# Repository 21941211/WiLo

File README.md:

# WiLo
Full documentation of the WiLo (Wireless Logger) LoRa enabled environmental monitoring logger.

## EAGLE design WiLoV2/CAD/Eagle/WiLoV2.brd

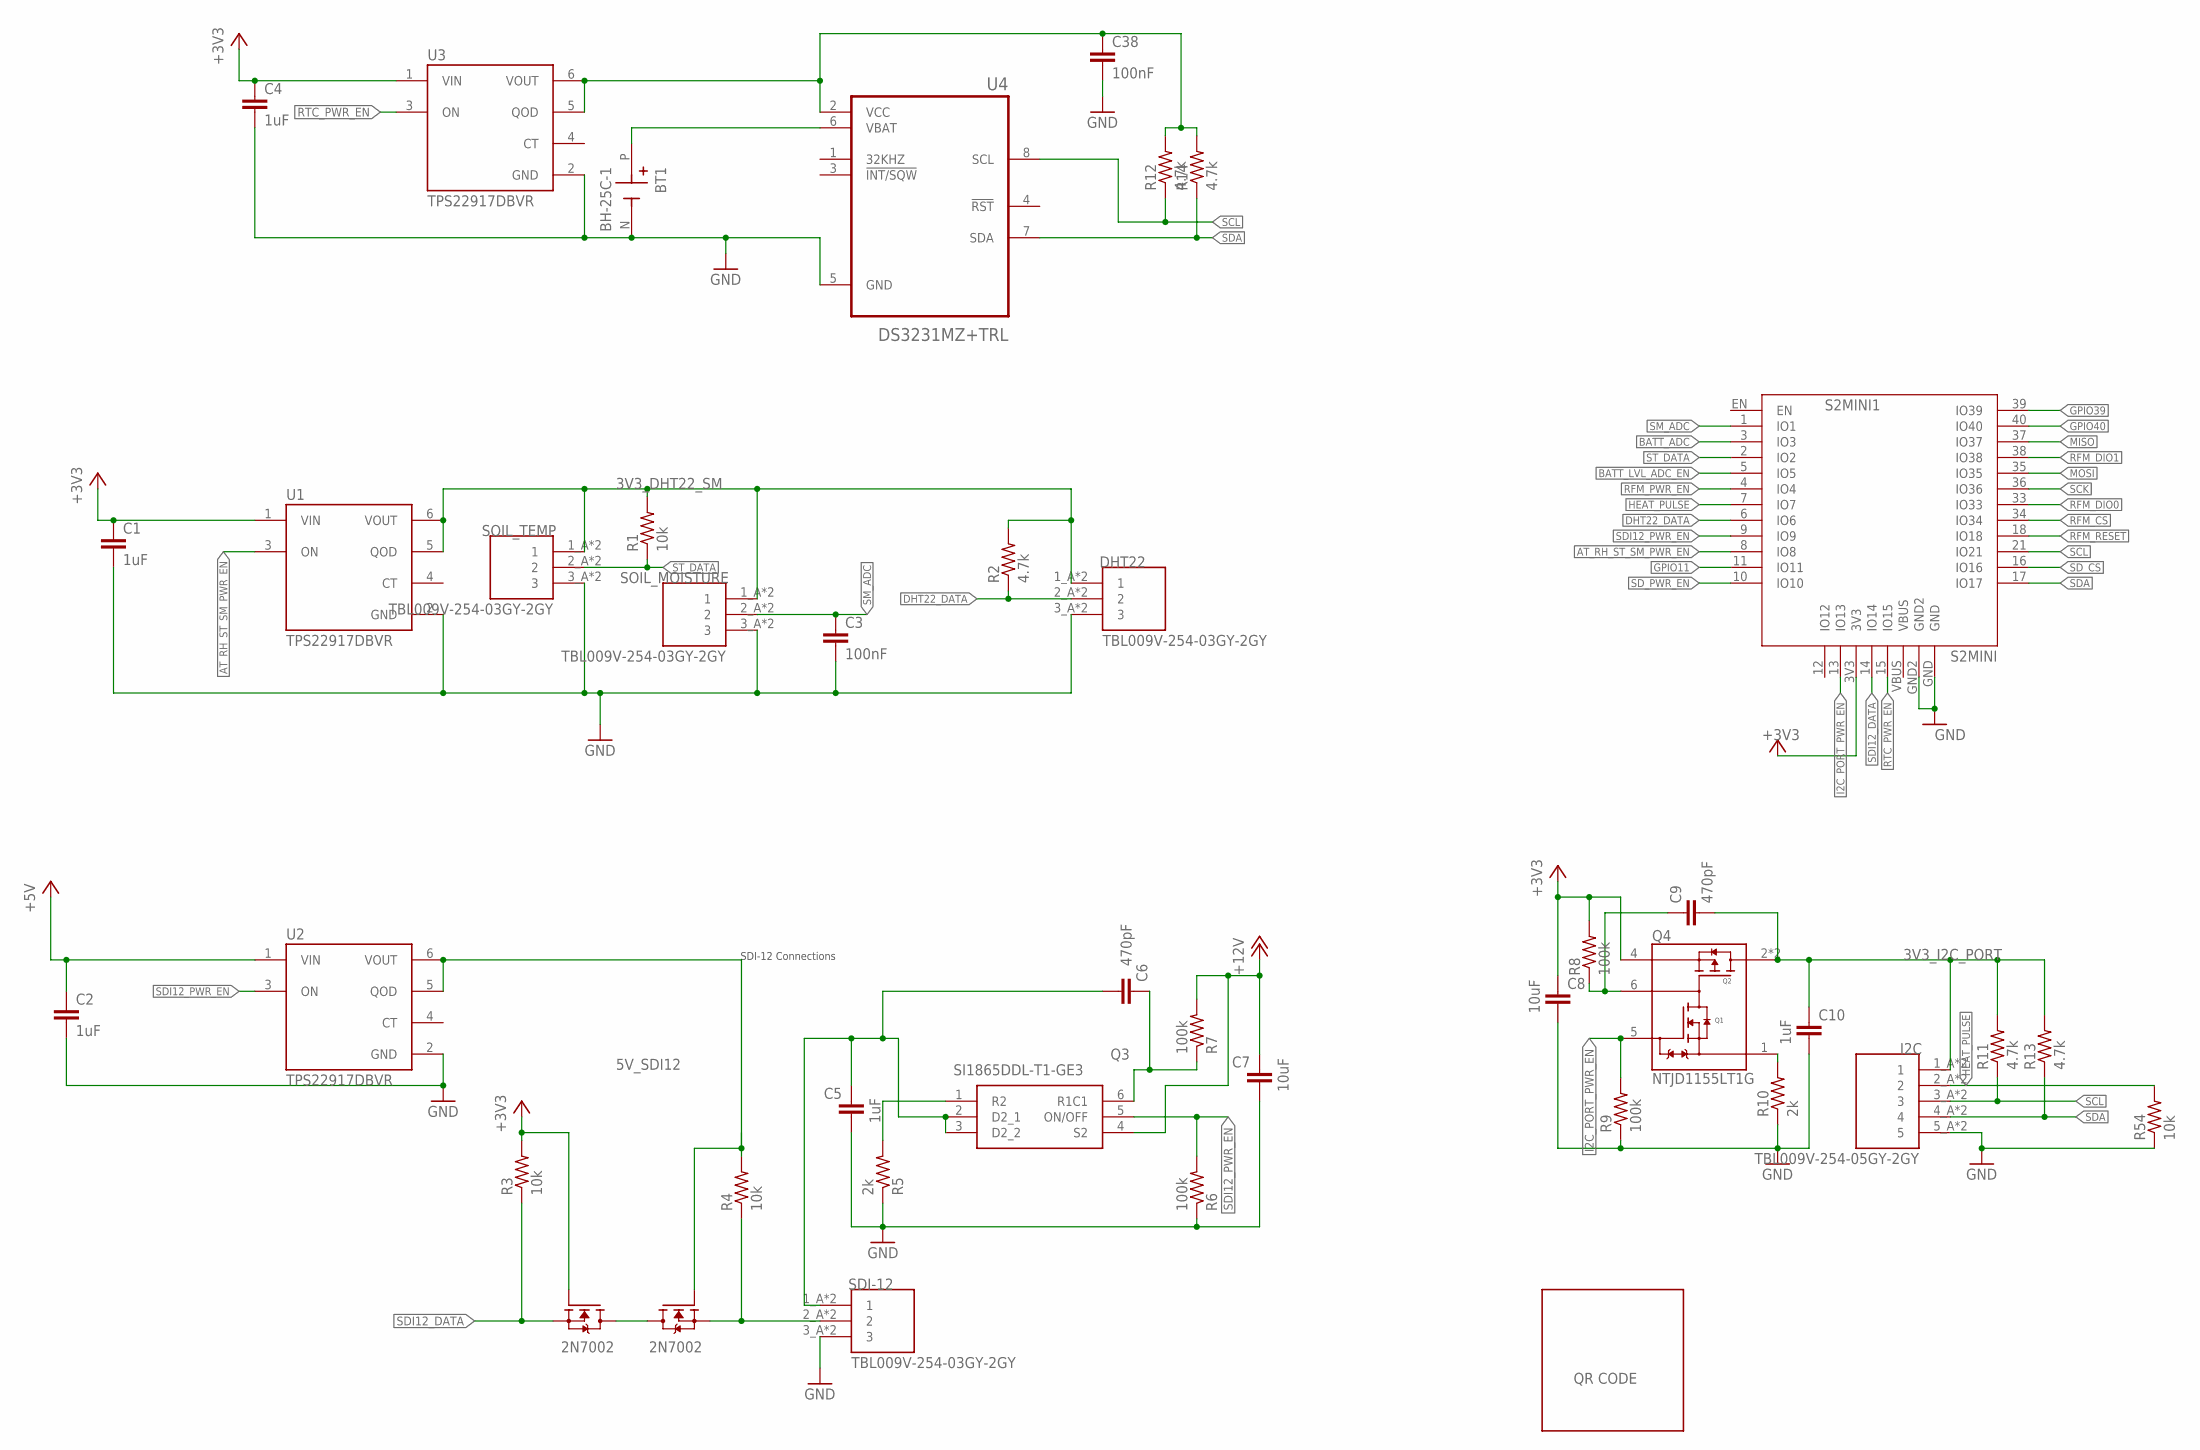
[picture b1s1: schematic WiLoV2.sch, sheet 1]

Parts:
BT1: BH-25C-1; BAT_BH-25C-1; MPN BH-25C-1
C1, C2, C4, C5, C10: 1uF; C0805; MPN CC0805KKX7R9BB105
C3, C38: 100nF; C0805; MPN KGM21NR71E104KT
C6, C9: 470pF; C0805; MPN CC0805JRNPOBBN471
C7, C8: 10uF; C0805; MPN GRM21BR61C106KE15K
DHT22: TBL009V-254-03GY-2GY; CUI_TBL009V-254-03GY-2GY; MPN TBL009V-254-03GY-2GY
I2C: TBL009V-254-05GY-2GY; CUI_TBL009V-254-05GY-2GY; MPN TBL009V-254-05GY-2GY
Q1, Q2: 2N7002; SOT95P240X111-3N; MPN 2N7002
Q3: SI1865DDL-T1-GE3; SOT65P210X110-6N; MPN SI1865DDL-T1-GE3
Q4: NTJD1155LT1G; TRANS_NTJD1155LT1G; MPN NTJD1155LT1G
QR_CODE: QR_CODE
R1, R3, R4, R54: 10k; R0603; MPN ERJ-U03F1002V
R2, R11, R12, R13, R14: 4.7k; R0603; MPN RK73G1JTTD4701C
R5, R10: 2k; R0603; MPN RC0603FR-072KL
R6, R7, R8, R9: 100k; R0603; MPN CRG0603F100K
S2MINI1: S2MINI
SDI-12: TBL009V-254-03GY-2GY; CUI_TBL009V-254-03GY-2GY; MPN TBL009V-254-03GY-2GY
SOIL_MOISTURE: TBL009V-254-03GY-2GY; CUI_TBL009V-254-03GY-2GY; MPN TBL009V-254-03GY-2GY
SOIL_TEMP: TBL009V-254-03GY-2GY; CUI_TBL009V-254-03GY-2GY; MPN TBL009V-254-03GY-2GY
U1, U2, U3: TPS22917DBVR; SOT95P280X145-6N; MPN TPS22917DBVT
U4: DS3231MZ+TRL; SOIC127P600X175-8N; MPN DS3231MZ+TRL

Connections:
3V3_DHT22_SM: DHT22.1_A (1), DHT22.1_B (1), R1.2, R2.2, SOIL_MOISTURE.1_A (1), SOIL_MOISTURE.1_B (1), SOIL_TEMP.1_A (1), SOIL_TEMP.1_B (1), U1.5 (QOD), U1.6 (VOUT)
3V3_I2C_PORT: C9.2, C10.1, I2C.1_A (1), I2C.1_B (1), Q4.2 (D2), Q4.3 (D2), R11.2, R13.2
5V_SDI12: Q2.1 (G), R4.2, U2.5 (QOD), U2.6 (VOUT)
+3V3: C1.1, C4.1, C8.1, Q1.1 (G), Q4.4 (S2), R3.2, R8.2, S2MINI1.3V3, U1.1 (VIN), U3.1 (VIN); also elsewhere on the board
+5V: C2.1, U2.1 (VIN); also elsewhere on the board
+12V: C7.1, Q3.4 (S2), R7.2; also elsewhere on the board
AT_RH_ST_SM_PWR_EN: S2MINI1.8 (IO8), U1.3 (ON)
BATT_ADC: S2MINI1.3 (IO3); also elsewhere on the board
BATT_LVL_ADC_EN: S2MINI1.5 (IO5); also elsewhere on the board
DHT22_DATA: DHT22.2_A (2), DHT22.2_B (2), R2.1, S2MINI1.6 (IO6)
GND: BT1.N, C1.2, C2.2, C3.2, C4.2, C5.2, C7.2, C8.2, C10.2, C38.2, DHT22.3_A (3), DHT22.3_B (3), I2C.5_A (5), I2C.5_B (5), R5.1, R6.1, R9.1, R10.1, R54.1, S2MINI1.GND, S2MINI1.GND2, SDI-12.3_A (3), SDI-12.3_B (3), SOIL_MOISTURE.3_A (3), SOIL_MOISTURE.3_B (3), SOIL_TEMP.3_A (3), SOIL_TEMP.3_B (3), U1.2 (GND), U2.2 (GND), U3.2 (GND), U4.5 (GND); also elsewhere on the board
GPIO11: S2MINI1.11 (IO11)
GPIO39: S2MINI1.39 (IO39)
GPIO40: S2MINI1.40 (IO40)
HEAT_PULSE: I2C.2_A (2), I2C.2_B (2), R54.2, S2MINI1.7 (IO7)
I2C_PORT_PWR_EN: Q4.5 (G1), R9.2, S2MINI1.13 (IO13)
MISO: S2MINI1.37 (IO37); also elsewhere on the board
MOSI: S2MINI1.35 (IO35); also elsewhere on the board
unnamed: Q1.3 (D), Q2.3 (D)
unnamed: C6.1, Q3.6 (R1C1), R7.1
unnamed: Q3.1 (R2), R5.2
unnamed: C9.1, Q4.6 (D1/G2), R8.1
unnamed: Q4.1 (S1), R10.2
unnamed: C5.1, C6.2, Q3.2 (D2_1), Q3.3 (D2_2), SDI-12.1_A (1), SDI-12.1_B (1)
unnamed: BT1.P, U4.6 (VBAT)
unnamed: C38.1, R12.2, R14.2, U3.5 (QOD), U3.6 (VOUT), U4.2 (VCC)
unnamed: Q2.2 (S), R4.1, SDI-12.2_A (2), SDI-12.2_B (2)
RFM_CS: S2MINI1.34 (IO34); also elsewhere on the board
RFM_DIO0: S2MINI1.33 (IO33); also elsewhere on the board
RFM_DIO1: S2MINI1.38 (IO38); also elsewhere on the board
RFM_PWR_EN: S2MINI1.4 (IO4); also elsewhere on the board
RFM_RESET: S2MINI1.18 (IO18); also elsewhere on the board
RTC_PWR_EN: S2MINI1.15 (IO15), U3.3 (ON)
SCK: S2MINI1.36 (IO36); also elsewhere on the board
SCL: I2C.3_A (3), I2C.3_B (3), R11.1, R12.1, S2MINI1.21 (IO21), U4.8 (SCL)
SDA: I2C.4_A (4), I2C.4_B (4), R13.1, R14.1, S2MINI1.17 (IO17), U4.7 (SDA)
SDI12_DATA: Q1.2 (S), R3.1, S2MINI1.14 (IO14)
SDI12_PWR_EN: Q3.5 (ON/OFF), R6.2, S2MINI1.9 (IO9), U2.3 (ON)
SD_CS: S2MINI1.16 (IO16); also elsewhere on the board
SD_PWR_EN: S2MINI1.10 (IO10); also elsewhere on the board
SM_ADC: C3.1, S2MINI1.1 (IO1), SOIL_MOISTURE.2_A (2), SOIL_MOISTURE.2_B (2)
ST_DATA: R1.1, S2MINI1.2 (IO2), SOIL_TEMP.2_A (2), SOIL_TEMP.2_B (2)

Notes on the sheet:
SDI-12 Connections

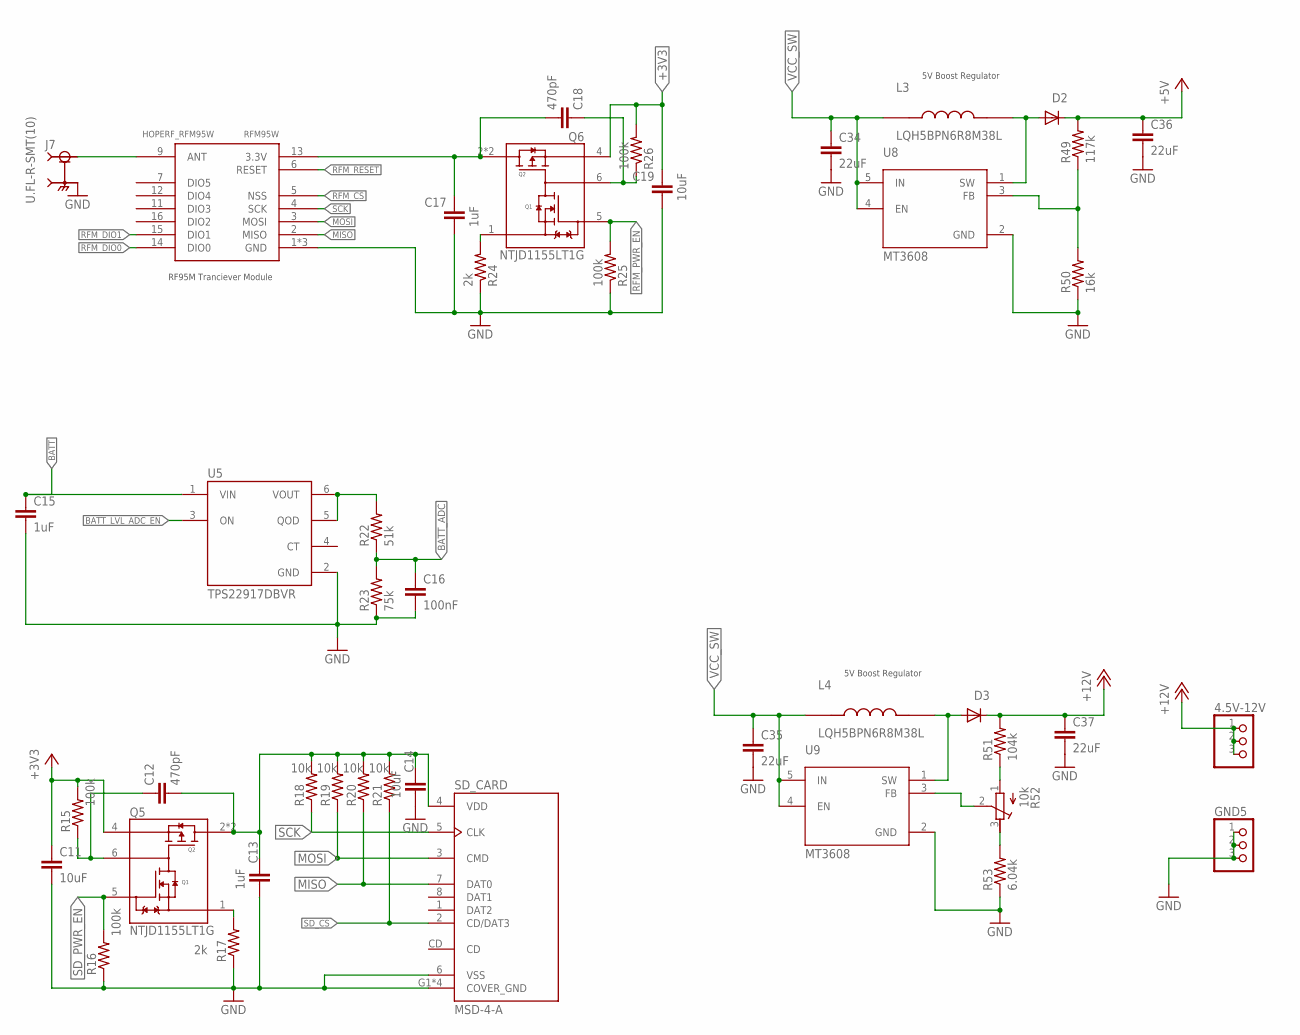
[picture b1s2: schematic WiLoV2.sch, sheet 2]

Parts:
4.5V-12V: PINHD-1X3; 1X03; MPN 61300311121
C11, C14, C19: 10uF; C0805; MPN GRM21BR61C106KE15K
C12, C18: 470pF; C0805; MPN CC0805JRNPOBBN471
C13, C15, C17: 1uF; C0805; MPN CC0805KKX7R9BB105
C16: 100nF; C0805; MPN KGM21NR71E104KT
C34, C35, C36, C37: 22uF; C0805; MPN CL21A226MOQNNNE
D2, D3: DIODE_SOD-123FL; SOD-123FL; MPN MBR120VLSFT1G
GND5: PINHD-1X3; 1X03; MPN 61300311121
J7: U.FL-R-SMT(10); HRS_U.FL-R-SMT(10); MPN U.FL-R-SMT-1(01)
L3, L4: LQH5BPN6R8M38L; IND_LQH5BPN6R8M38L; MPN LQH5BPN6R8M38L
Q5, Q6: NTJD1155LT1G; TRANS_NTJD1155LT1G; MPN NTJD1155LT1G
R15, R16, R25, R26: 100k; R0603; MPN CRG0603F100K
R17, R24: 2k; R0603; MPN RC0603FR-072KL
R18, R19, R20, R21: 10k; R0603; MPN ERJ-U03F1002V
R22: 51k; R0603; MPN RC0603FR-0751KL
R23: 75k; R0603; MPN AC0603FR-0775KL
R49: 117k; R0603; MPN RT0603DRE07117KL
R50: 16k; R0603; MPN RC0603FR-0716KL
R51: 104k; R0603; MPN RN73H1JTTD1043B50
R52: 10k; RTRIM3296W; MPN 3296W-1-103RLF
R53: 6.04k; R0603; MPN ERJ-3EKF6041V
RFM95W: HOPERF_RFM95W; MPN RFM95W-868S2
SD_CARD: MSD-4-A; CUI_MSD-4-A; MPN MSD-4-A
U5: TPS22917DBVR; SOT95P280X145-6N; MPN TPS22917DBVT
U8, U9: MT3608; SOT95P280X145-6N; MPN MT3608

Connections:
+3V3: C11.1, C19.1, Q5.4 (S2), Q6.4 (S2), R15.2, R26.2; also elsewhere on the board
+5V: C36.1, D2.C, R49.2; also elsewhere on the board
+12V: 4.5V-12V.1, 4.5V-12V.2, 4.5V-12V.3, C37.1, D3.C, R51.2; also elsewhere on the board
BATT: C15.1, U5.1 (VIN); also elsewhere on the board
BATT_ADC: C16.1, R22.1, R23.2; also elsewhere on the board
BATT_LVL_ADC_EN: U5.3 (ON); also elsewhere on the board
GND: C11.2, C13.2, C14.2, C15.2, C16.2, C17.2, C19.2, C34.2, C35.2, C36.2, C37.2, GND5.1, GND5.2, GND5.3, J7.2 (GND), J7.3 (GND), R16.1, R17.1, R23.1, R24.1, R25.1, R50.1, R53.1, RFM95W.1 (GND), RFM95W.8 (GND), RFM95W.10 (GND), SD_CARD.6 (VSS), SD_CARD.G1 (COVER_GND), SD_CARD.G2 (COVER_GND), SD_CARD.G3 (COVER_GND), SD_CARD.G4 (COVER_GND), U5.2 (GND), U8.2 (GND), U9.2 (GND); also elsewhere on the board
MISO: R20.1, RFM95W.2 (MISO), SD_CARD.7 (DAT0); also elsewhere on the board
MOSI: R19.1, RFM95W.3 (MOSI), SD_CARD.3 (CMD); also elsewhere on the board
unnamed: R22.2, U5.5 (QOD), U5.6 (VOUT)
unnamed: R51.1, R52.1 (A)
unnamed: D3.A, L4.2, U9.1 (SW)
unnamed: R52.2 (S), U9.3 (FB)
unnamed: R52.3 (E), R53.2
unnamed: C12.1, Q5.6 (D1/G2), R15.1
unnamed: Q5.1 (S1), R17.2
unnamed: D2.A, L3.2, U8.1 (SW)
unnamed: J7.1 (SIG), RFM95W.9 (ANT)
unnamed: R49.1, R50.2, U8.3 (FB)
unnamed: C12.2, C13.1, C14.1, Q5.2 (D2), Q5.3 (D2), R18.2, R19.2, R20.2, R21.2, SD_CARD.4 (VDD)
unnamed: C18.1, Q6.6 (D1/G2), R26.1
unnamed: Q6.1 (S1), R24.2
unnamed: C17.1, C18.2, Q6.2 (D2), Q6.3 (D2), RFM95W.13 (3.3V)
RFM_CS: RFM95W.5 (NSS); also elsewhere on the board
RFM_DIO0: RFM95W.14 (DIO0); also elsewhere on the board
RFM_DIO1: RFM95W.15 (DIO1); also elsewhere on the board
RFM_PWR_EN: Q6.5 (G1), R25.2; also elsewhere on the board
RFM_RESET: RFM95W.6 (RESET); also elsewhere on the board
SCK: R18.1, RFM95W.4 (SCK), SD_CARD.5 (CLK); also elsewhere on the board
SD_CS: R21.1, SD_CARD.2 (CD/DAT3); also elsewhere on the board
SD_PWR_EN: Q5.5 (G1), R16.2; also elsewhere on the board
VCC_SW: C34.1, C35.1, L3.1, L4.1, U8.4 (EN), U8.5 (IN), U9.4 (EN), U9.5 (IN); also elsewhere on the board

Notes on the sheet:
RF95M Tranciever Module
5V Boost Regulator

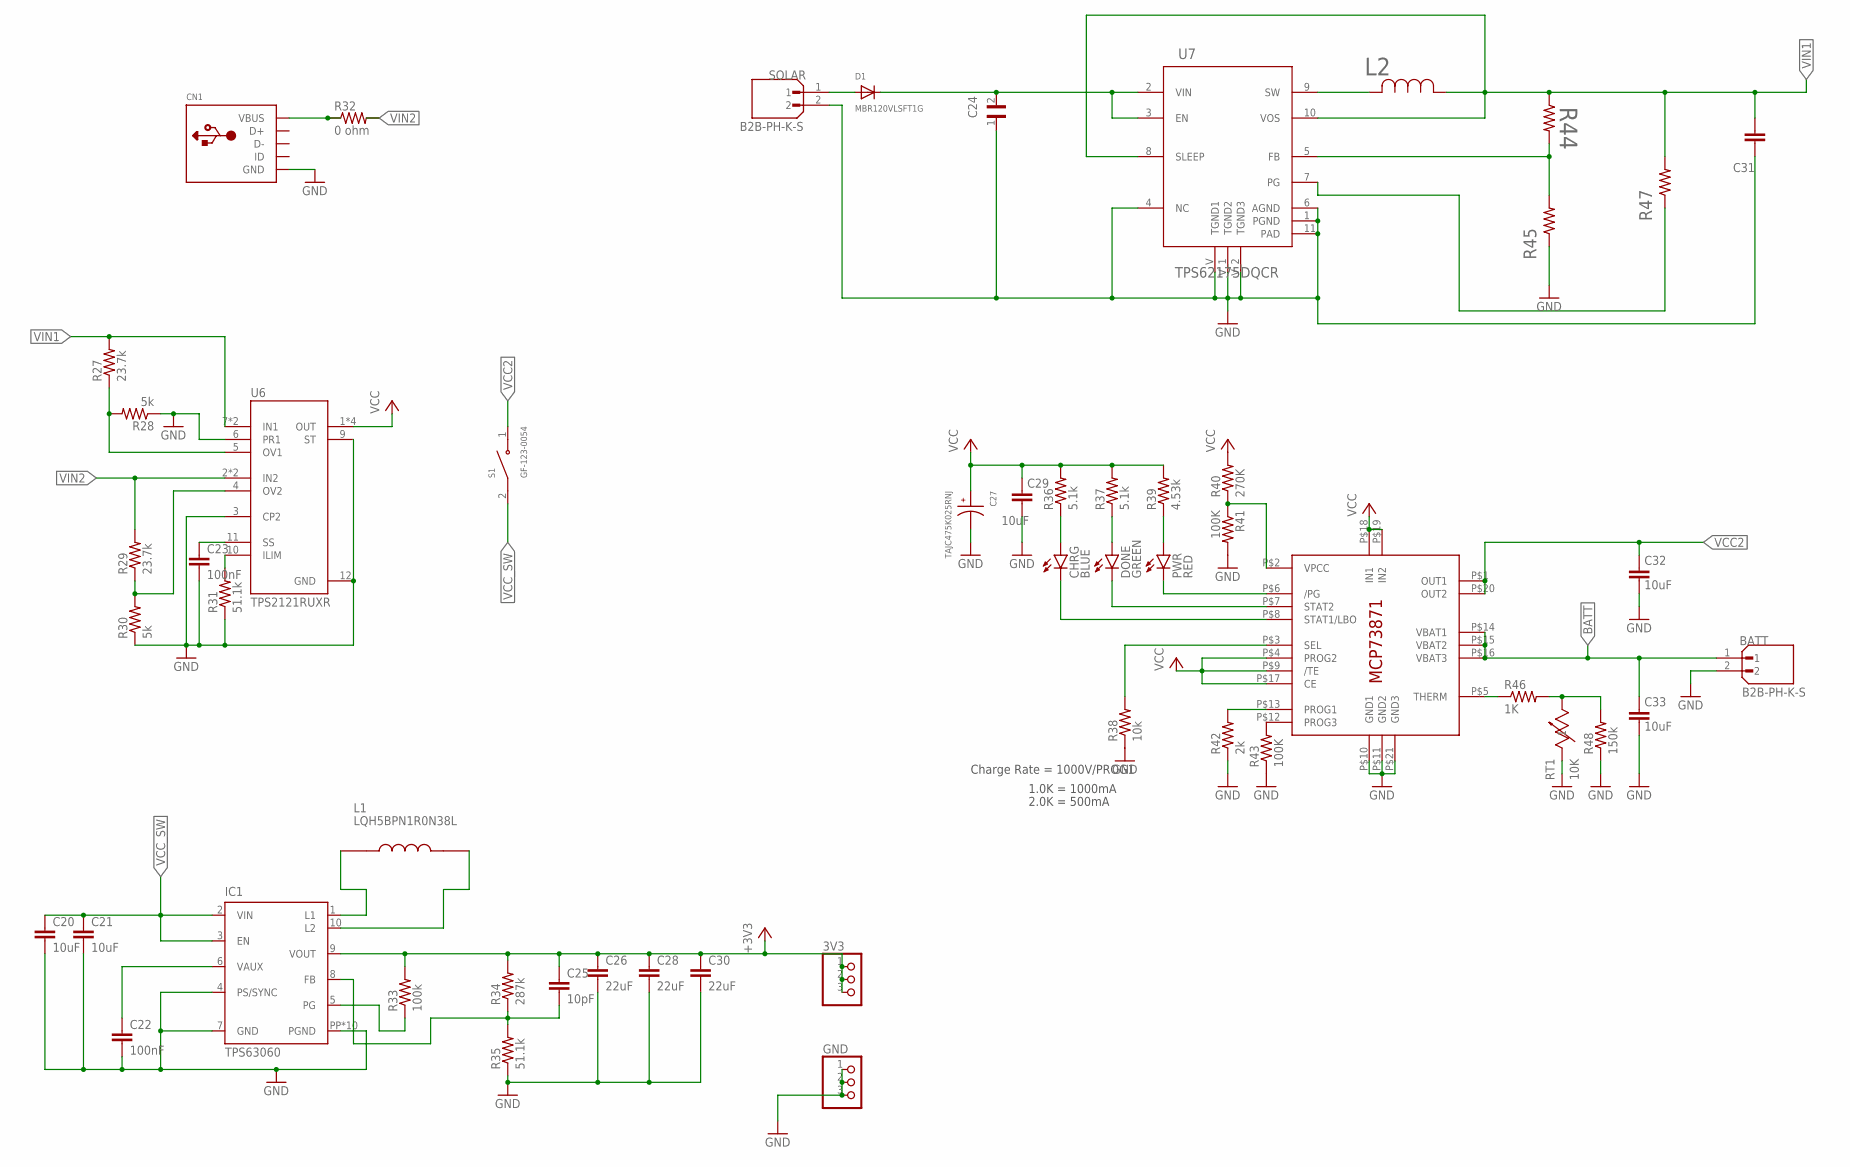
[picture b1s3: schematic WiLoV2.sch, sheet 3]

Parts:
3V3: PINHD-1X3; 1X03; MPN 61300311121
BATT: B2B-PH-K-S; JST_B2B-PH-K-S; MPN B2B-PH-K-S
C20, C21, C29, C32, C33: 10uF; C0805; MPN GRM21BR61C106KE15K
C22, C23: 100nF; C0805; MPN KGM21NR71E104KT
C24: 2.2uF; CAPC2012X145N; MPN CGA4J3X7R1H225K125AB
C25: 10pF; C0805; MPN C0805C100JDGACTU
C26, C28, C30, C31: 22uF; C0805; MPN CL21A226MOQNNNE
C27: TAJC475K025RNJ; CAPPM6032X280N; MPN TAJC475K025RNJ
CHRG: BLUE; SML0603; MPN XZCFBB53W-8VF
CN1: USBMINIB; USB-MINIB; MPN 690-005-299-043
D1: MBR120VLSFT1G; SOD-123FL; MPN MBR120VLSFT1G
DONE: GREEN; SML0603; MPN XZCDGK53W-8VF
GND: PINHD-1X3; 1X03; MPN 61300311121
IC1: TPS63060; DSC-S-PWSON-N10; MPN TPS63060DSCR
IC2: MCP73871; QFN20_4MM; MPN MCP73871T-2CCI/ML
L1: LQH5BPN1R0N38L; IND_LQH5BPN1R0N38L; MPN LQH5BPN1R0N38L
L2: 10uH; IND_IFSC_1515AH_VIS-M; MPN IFSC1515AHER100M01
PWR: RED; SML0603; MPN XZCM2CRK53WA-8VF
R27, R29: 23.7k; R0603; MPN ERJ-3EKF2372V
R28, R30: 5k; R0603; MPN RN73A1J5K0FTD
R31, R35: 51.1k; R0603; MPN RC0603FR-0751K1L
R32: 0 ohm; R0805; MPN ERJ-6GEY0R00V
R33, R47: 100k; R0603; MPN CRG0603F100K
R34: 287k; R0603; MPN ERJ-3EKF2873V
R36, R37: 5.1k; R0603; MPN ERA-3ARW512V
R38: 10k; R0603; MPN ERJ-U03F1002V
R39: 4.53k; R0603; MPN ERJ-3EKF4531V
R40: 270K; R0603; MPN ERJ-3EKF2703V
R41, R43: 100K; R0805; MPN RC0805FR-07100KL
R42: 2k; R0603; MPN RC0603FR-072KL
R44: 105k; R0603; MPN AC0603FR-07105KL
R45: 20k; R0603; MPN RC0603FR-0720KL
R46: 1K; R0603; MPN RMCF0603FT1K00
R48: 150k; R0603; MPN ERJ-3EKF1503V
RT1: 10K; G1_USS; MPN 103JG1F
S1: GF-123-0054; SW_GF-123-0054; MPN GF-123-0054
SOLAR: B2B-PH-K-S; JST_B2B-PH-K-S; MPN B2B-PH-K-S
U6: TPS2121RUXR; IC_TPS2121RUXR; MPN TPS2121RUXR
U7: TPS62175DQCR; DQC0010A; MPN TPS62175DQCR

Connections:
+3V3: 3V3.1, 3V3.2, 3V3.3, C25.1, C26.1, C28.1, C30.1, IC1.9 (VOUT), R33.2, R34.2; also elsewhere on the board
BATT: BATT.1, C33.1, IC2.P$14 (VBAT1), IC2.P$15 (VBAT2), IC2.P$16 (VBAT3); also elsewhere on the board
GND: BATT.2, C20.2, C21.2, C22.2, C23.2, C24.1, C26.2, C27.2, C28.2, C29.2, C30.2, C31.1, C32.2, C33.2, CN1.GND, GND.1, GND.2, GND.3, IC1.4 (PS/SYNC), IC1.7 (GND), IC1.PP (PGND), IC1.PP@1 (PGND), IC1.PP@2 (PGND), IC1.PP@3 (PGND), IC1.PP@4 (PGND), IC1.PP@5 (PGND), IC1.PP@7 (PGND), IC1.PP@8 (PGND), IC1.PP@9 (PGND), IC1.PP@10 (PGND), IC2.P$10 (GND1), IC2.P$11 (GND2), IC2.P$21 (GND3), R28.1, R30.1, R31.1, R35.1, R38.1, R41.2, R42.1, R43.1, R45.1, R48.1, RT1.1, SOLAR.2, U6.3 (CP2), U6.6 (PR1), U6.9 (ST), U6.12 (GND), U7.1 (PGND), U7.4 (NC), U7.6 (AGND), U7.11 (PAD), U7.V (TGND1), U7.V_1 (TGND2), U7.V_2 (TGND3); also elsewhere on the board
unnamed: IC1.1 (L1), L1.1
unnamed: IC1.10 (L2), L1.2
unnamed: C22.1, IC1.6 (VAUX)
unnamed: IC1.5 (PG), R33.1
unnamed: IC2.P$6 (/PG), PWR.C
unnamed: DONE.C, IC2.P$7 (STAT2)
unnamed: CHRG.C, IC2.P$8 (STAT1/LBO)
unnamed: CHRG.A, R36.1
unnamed: DONE.A, R37.1
unnamed: PWR.A, R39.1
unnamed: IC2.P$12 (PROG3), R43.2
unnamed: IC2.P$13 (PROG1), R42.2
unnamed: C24.2, D1.C, U7.2 (VIN), U7.3 (EN)
unnamed: IC2.P$5 (THERM), R46.1
unnamed: R46.2, R48.2, RT1.2
unnamed: CN1.VBUS, R32.1
unnamed: C25.2, IC1.8 (FB), R34.1, R35.2
unnamed: L2.2, U7.9 (SW)
unnamed: R44.2, R45.2, U7.5 (FB)
unnamed: R47.1, U7.7 (PG)
unnamed: R27.1, R28.2, U6.5 (OV1)
unnamed: R29.1, R30.2, U6.4 (OV2)
unnamed: R31.2, U6.10 (ILIM)
unnamed: C23.1, U6.11 (SS)
unnamed: IC2.P$3 (SEL), R38.2
unnamed: D1.A, SOLAR.1
VCC: C27.1, C29.1, IC2.P$4 (PROG2), IC2.P$9 (/TE), IC2.P$17 (CE), IC2.P$18 (IN1), IC2.P$19 (IN2), R36.2, R37.2, R39.2, R40.2, U6.1 (OUT), U6.1_1 (OUT), U6.8 (OUT), U6.8_1 (OUT)
VCC2: C32.1, IC2.P$1 (OUT1), IC2.P$20 (OUT2), S1.1
VCC_SW: C20.1, C21.1, IC1.2 (VIN), IC1.3 (EN), S1.2; also elsewhere on the board
VIN1: C31.2, L2.1, R27.2, R44.1, R47.2, U6.7 (IN1), U6.7_1 (IN1), U7.8 (SLEEP), U7.10 (VOS)
VIN2: R29.2, R32.2, U6.2 (IN2), U6.2_1 (IN2)
VPCC: IC2.P$2 (VPCC), R40.1, R41.1

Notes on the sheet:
Charge Rate = 1000V/PROG1
1.0K = 1000mA
2.0K = 500mA

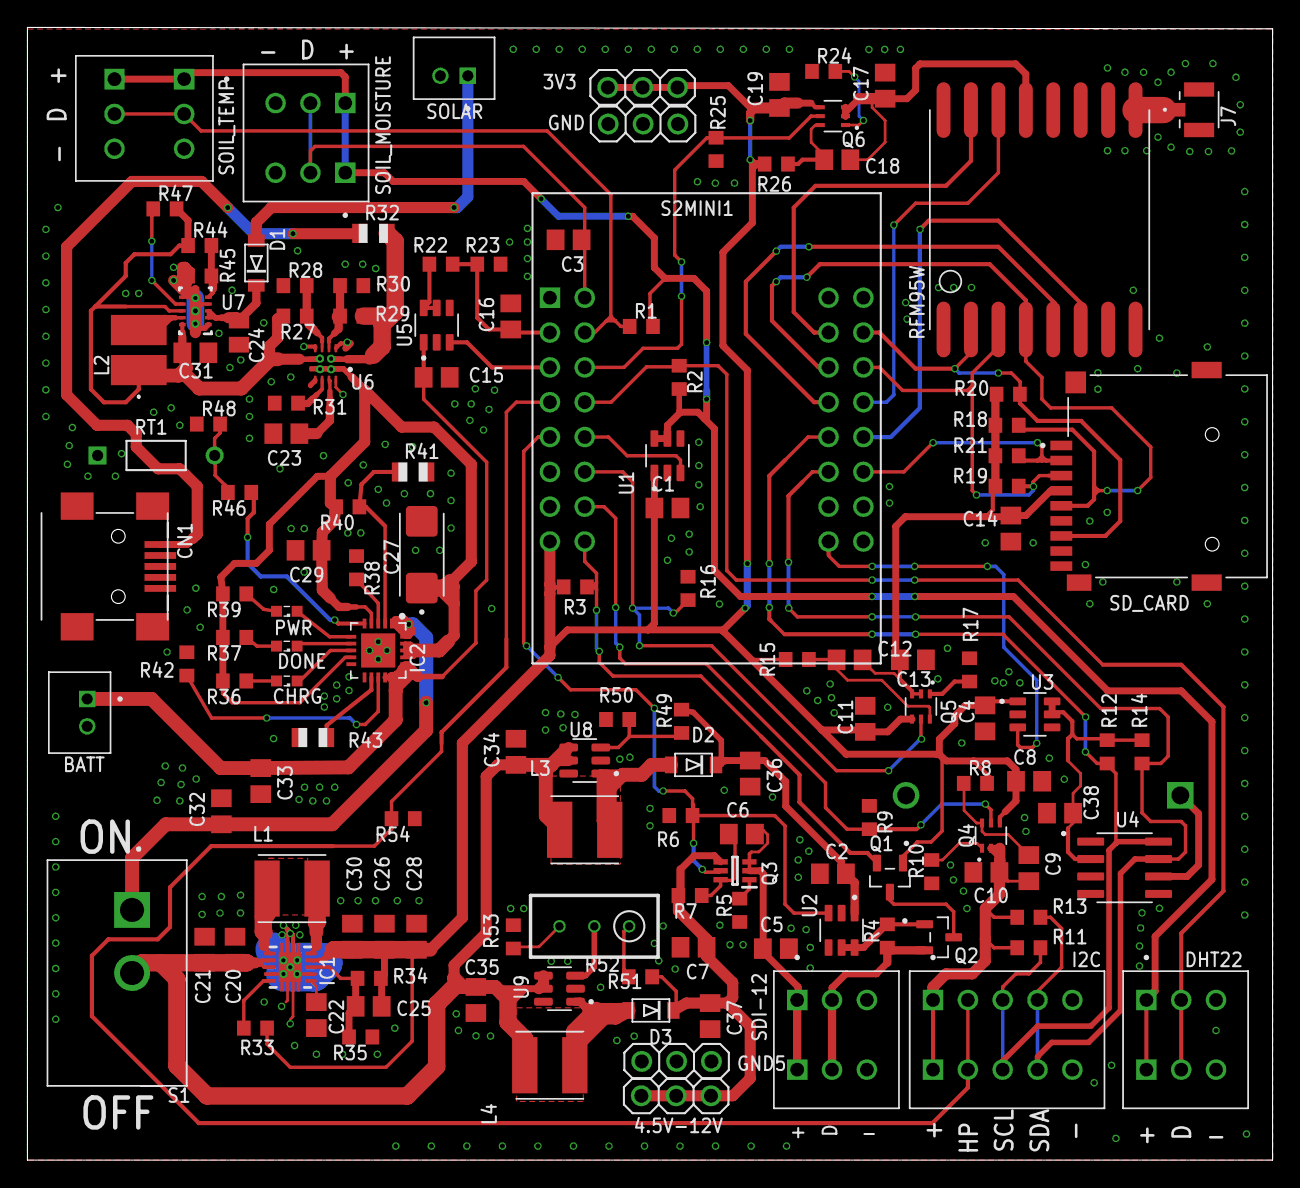
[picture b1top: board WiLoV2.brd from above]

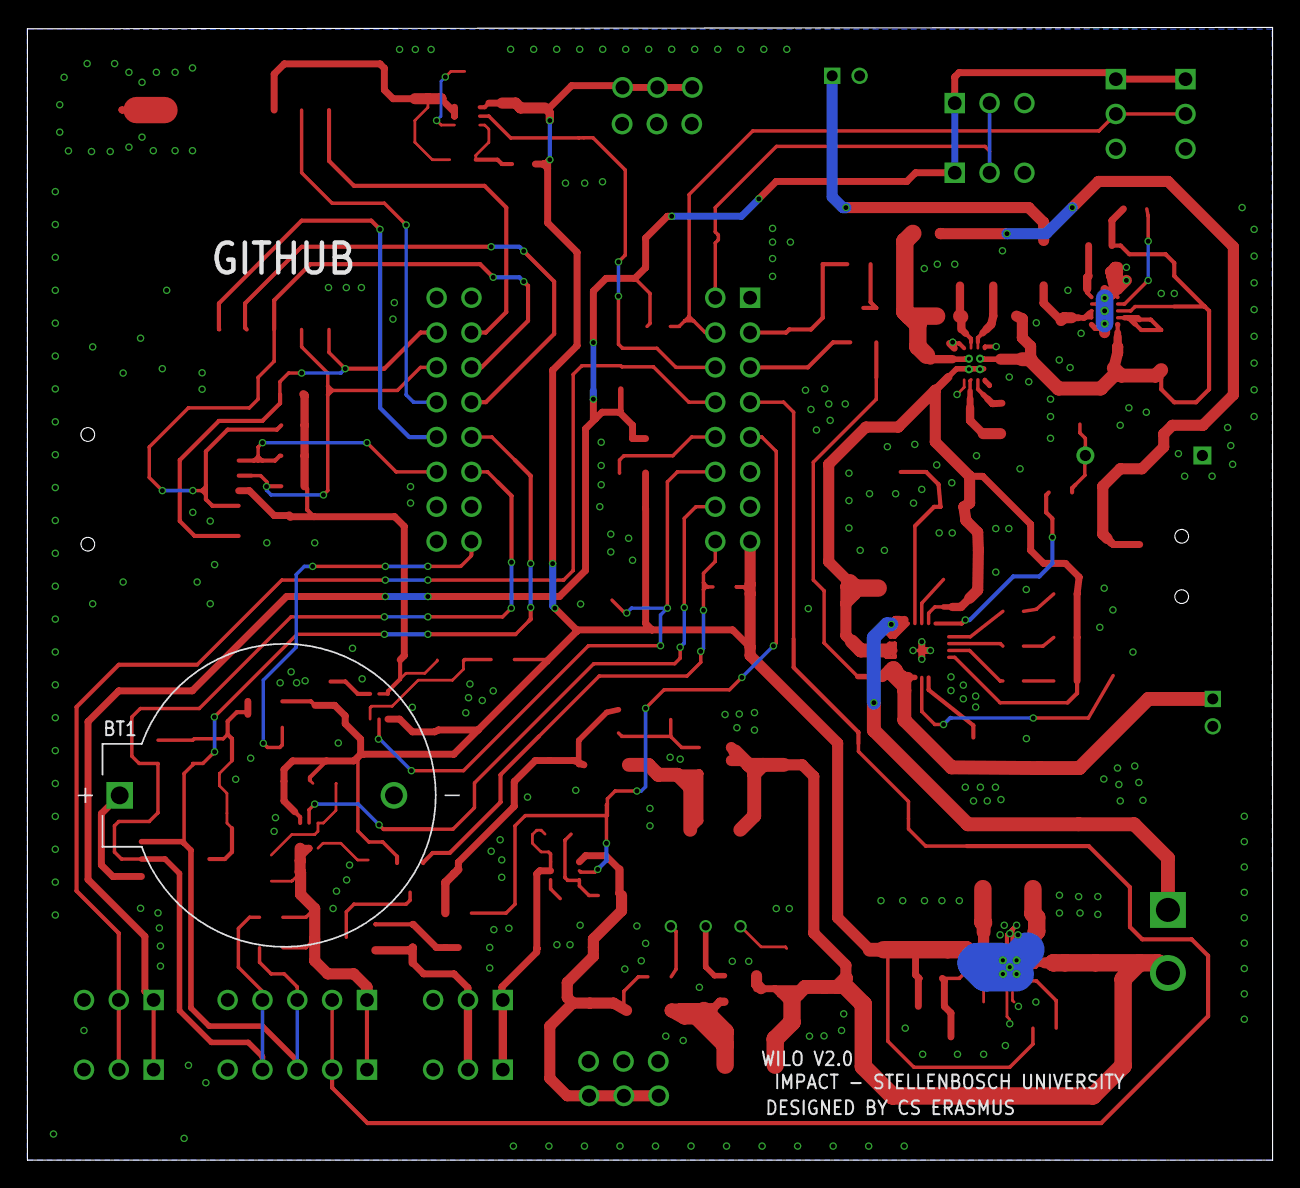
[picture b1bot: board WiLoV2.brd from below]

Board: 2 copper layers, 90.8 x 82.6 mm, 139 parts (2 on the bottom side), 86 nets.

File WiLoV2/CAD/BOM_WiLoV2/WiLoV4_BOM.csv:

Qty;Value;Device;Package;Parts;MPN
2;;DIODE_SOD-123FL;SOD-123FL;D2, D3;MBR120VLSFT1G
4;;PINHD-1X3;1X03;3V3, 4.5V-12V, GND, GND5;61300311121
1;;USBMINIB;USB-MINIB;CN1;690-005-299-043
1;0 ohm;R-US_R0805;R0805;R32;ERJ-6GEY0R00V
2;100K;R-US_R0805;R0805;R41, R43;RC0805FR-07100KL
10;100k;R-US_R0603;R0603;R6, R7, R8, R9, R15, R16, R25, R26, R33, R47;CRG0603F100K
5;100nF;C-EUC0805;C0805;C3, C16, C22, C23, C38;KGM21NR71E104KT
1;104k;R-US_R0603;R0603;R51;RN73H1JTTD1043B50
1;105k;R-US_R0603;R0603;R44;AC0603FR-07105KL
1;10K;103JG1F;G1_USS;RT1;103JG1F
1;10k;R-TRIMM3296W;RTRIM3296W;R52;3296W-1-103RLF
9;10k;R-US_R0603;R0603;R1, R3, R4, R18, R19, R20, R21, R38, R54;ERJ-U03F1002V
1;10pF;C-EUC0805;C0805;C25;C0805C100JDGACTU
10;10uF;C-EUC0805;C0805;C7, C8, C11, C14, C19, C20, C21, C29, C32, C33;GRM21BR61C106KE15K
1;10uH;IFSC1515AHER100M01IND_IFSC_1515AH_VIS-M;IND_IFSC_1515AH_VIS-M;L2;IFSC1515AHER100M01
1;117k;R-US_R0603;R0603;R49;RT0603DRE07117KL
1;150k;R-US_R0603;R0603;R48;ERJ-3EKF1503V
1;16k;R-US_R0603;R0603;R50;3296W-1-103RLF
1;1K;R-US_R0603;R0603;R46;RMCF0603FT1K00
8;1uF;C-EUC0805;C0805;C1, C2, C4, C5, C10, C13, C15, C17;CC0805KKX7R9BB105
1;2.2uF;CGA4J3X7R1H225K125AB;CAPC2012X145N;C24;CGA4J3X7R1H225K125AB
1;20k;R-US_R0603;R0603;R45;RC0603FR-0720KL
8;22uF;C-EUC0805;C0805;C26, C28, C30, C31, C34, C35, C36, C37;CL21A226MOQNNNE
2;23.7k;R-US_R0603;R0603;R27, R29;ERJ-3EKF2372V
1;270K;R-US_R0603;R0603;R40;ERJ-3EKF2703V
1;287k;R-US_R0603;R0603;R34;ERJ-3EKF2873V
2;2N7002;2N7002;SOT95P240X111-3N;Q1, Q2;2N7002
5;2k;R-US_R0603;R0603;R5, R10, R17, R24, R42;RC0603FR-072KL
1;4.53k;R-US_R0603;R0603;R39;ERJ-3EKF4531V
5;4.7k;R-US_R0603;R0603;R2, R11, R12, R13, R14;RK73G1JTTD4701C
4;470pF;C-EUC0805;C0805;C6, C9, C12, C18;CC0805JRNPOBBN471
2;5.1k;R-US_R0603;R0603;R36, R37;ERA-3ARW512V
2;51.1k;R-US_R0603;R0603;R31, R35;ERJ-1GNF5112C
1;51k;R-US_R0603;R0603;R22;RC0603FR-0751KL
2;5k;R-US_R0603;R0603;R28, R30;RN73A1J5K0FTD
1;6k;R-US_R0603;R0603;R53;ERJ-3EKF6041V
1;75k;R-US_R0603;R0603;R23;AC0603FR-0775KL
2;B2B-PH-K-S;B2B-PH-K-S;JST_B2B-PH-K-S;BATT, SOLAR;B2B-PH-K-S
1;BH-25C-1;BH-25C-1;BAT_BH-25C-1;BT1;BH-25C-1
1;BLUE;LEDSML0603;SML0603;CHRG;XZCFBB53W-8VF
1;DS3231MZ+TRL;DS3231MZ+TRL;SOIC127P600X175-8N;U4;DS3231MZ+TRL
1;GF-123-0054;GF-123-0054;SW_GF-123-0054;S1;GF-123-0054
1;GREEN;LEDSML0603;SML0603;DONE;XZCDGK53W-8VF
1;HOPERF_RFM95W;HOPERF_RFM95W;HOPERF_RFM95W;RFM95W;RFM95W-868S2
1;LQH5BPN1R0N38L;LQH5BPN1R0N38L;IND_LQH5BPN1R0N38L;L1;LQH5BPN1R0N38L
2;LQH5BPN6R8M38L;LQH5BPN6R8M38L;IND_LQH5BPN6R8M38L;L3, L4;LQH5BPN6R8M38L
1;MBR120VLSFT1G;DIODE_SOD-123FL;SOD-123FL;D1;MBR120VLSFT1G
1;MCP73871;MCP73871;QFN20_4MM;IC2;MCP73871T-2CCI/ML
1;MSD-4-A;MSD-4-A;CUI_MSD-4-A;SD_CARD;MSD-4-A
2;MT3608;MT3608;SOT95P280X145-6N;U8, U9;MT3608
4;NTJD1155LT1G;NTJD1155LT1G;TRANS_NTJD1155LT1G;Q3, Q4, Q5, Q6;NTJD1155LT1G
1;QR_CODE;QR_CODE;QR_CODE;QR_CODE;
1;RED;LEDSML0603;SML0603;PWR;XZCM2CRK53WA-8VF
1;S2MINI;S2MINI;S2MINI;S2MINI1;SH2-16G
1;TAJC475K025RNJ;TAJC475K025RNJ;CAPPM6032X280N;C27;TAJC475K025RNJ
4;TBL009V-254-03GY-2GY;TBL009V-254-03GY-2GY;CUI_TBL009V-254-03GY-2GY;DHT22, SDI-12, SOIL_MOISTURE, SOIL_TEMP;TBL009V-254-03GY-2GY
1;TBL009V-254-05GY-2GY;TBL009V-254-05GY-2GY;CUI_TBL009V-254-05GY-2GY;I2C;TBL009V-254-05GY-2GY
1;TPS2121RUXR;TPS2121RUXR;IC_TPS2121RUXR;U6;TPS2121RUXR
4;TPS22917DBVR;TPS22917DBVR;SOT95P280X145-6N;U1, U2, U3, U5;TPS22917DBVT
1;TPS62175DQCR;TPS62175DQCR;DQC0010A;U7;TPS62175DQCR
1;TPS63060;TPS63060;DSC-S-PWSON-N10;IC1;TPS63060DSCR
1;U.FL-R-SMT(10);U.FL-R-SMT(10);HRS_U.FL-R-SMT(10);J7;U.FL-R-SMT-1(01)

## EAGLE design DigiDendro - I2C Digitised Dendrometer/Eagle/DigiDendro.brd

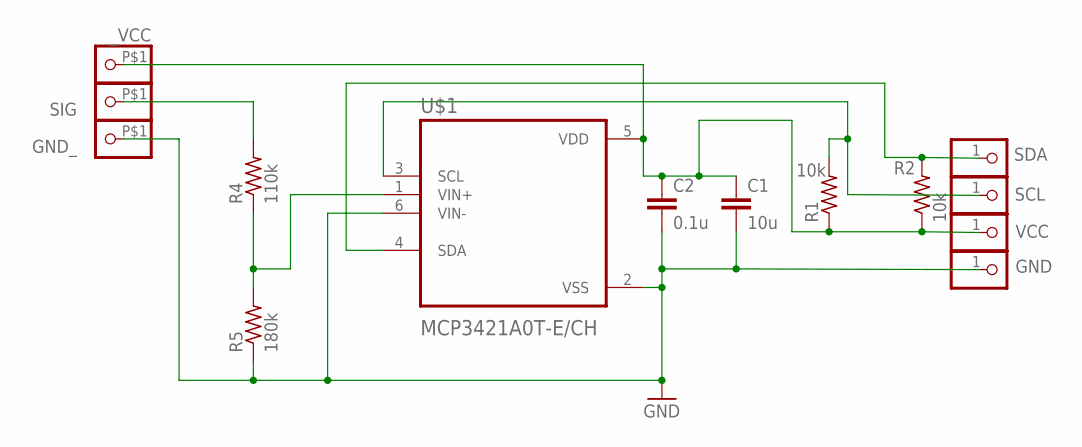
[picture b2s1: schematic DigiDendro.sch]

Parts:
C1: 10u; C0805
C2: 0.1u; C0805
GND: PINHD-1X1; 1X01
GND_: PINHD-1X1-BIGPOGO; 1X1-BIGPOGO
R1, R2: 10k; R0603
R4: 110k; R0603
R5: 180k; R0603
SCL: PINHD-1X1; 1X01
SDA: PINHD-1X1; 1X01
SIG: PINHD-1X1-BIGPOGO; 1X1-BIGPOGO
U$1: MCP3421A0T-E/CH; SOT95P280X145-6N
VCC: PINHD-1X1; 1X01
_VCC: PINHD-1X1-BIGPOGO; 1X1-BIGPOGO

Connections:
GND: C1.2, C2.2, GND.1, GND_.P$1, R5.1, U$1.2 (VSS), U$1.6 (VIN-)
unnamed: R4.2, SIG.P$1
unnamed: R4.1, R5.2, U$1.1 (VIN+)
SCL: R1.2, SCL.1, U$1.3 (SCL)
SDA: R2.2, SDA.1, U$1.4 (SDA)
VCC: C1.1, C2.1, R1.1, R2.1, U$1.5 (VDD), VCC.1, _VCC.P$1

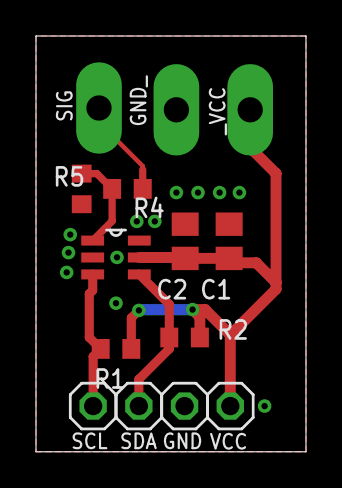
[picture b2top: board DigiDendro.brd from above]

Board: 2 copper layers, 15.0 x 23.1 mm, 14 parts (0 on the bottom side), 6 nets.

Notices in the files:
parts and their libraries:
COPYRIGHT: Copyright (C) 2025 Ultra Librarian. All rights reserved.
